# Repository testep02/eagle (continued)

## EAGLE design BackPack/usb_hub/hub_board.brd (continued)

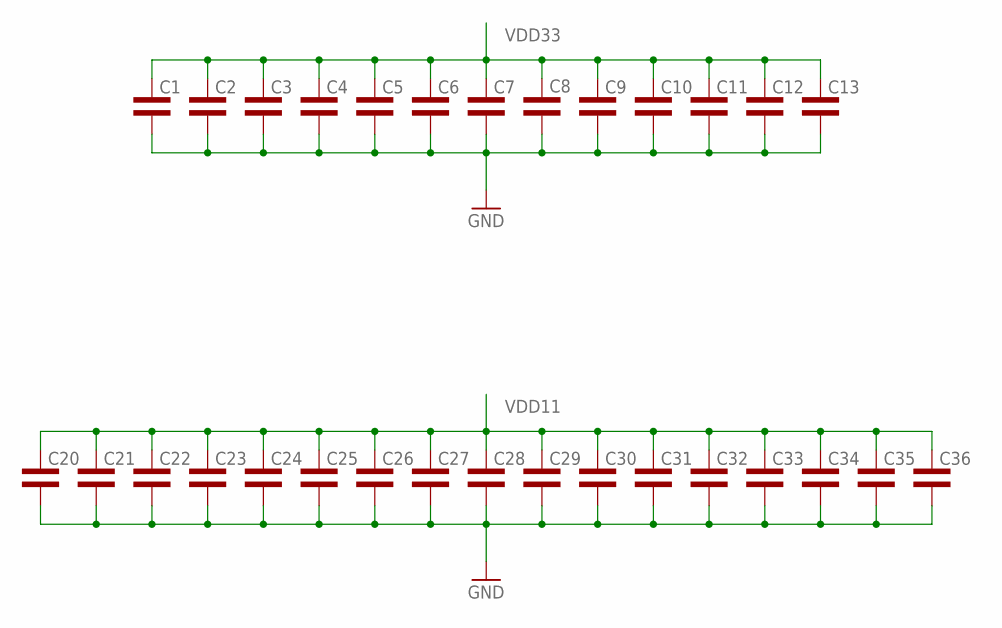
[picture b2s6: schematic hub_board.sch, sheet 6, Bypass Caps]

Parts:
C1, C2, C3, C4, C5, C6, C7, C8, C9, C10, C11, C12, C13, C20, C21, C22, C23, C24, C25, C26, C27, C28, C29, C30, C31, C32, C33, C34, C35, C36: CAP0402L3; 0402L3

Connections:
GND: C1.P$2 (2), C2.P$2 (2), C3.P$2 (2), C4.P$2 (2), C5.P$2 (2), C6.P$2 (2), C7.P$2 (2), C8.P$2 (2), C9.P$2 (2), C10.P$2 (2), C11.P$2 (2), C12.P$2 (2), C13.P$2 (2), C20.P$2 (2), C21.P$2 (2), C22.P$2 (2), C23.P$2 (2), C24.P$2 (2), C25.P$2 (2), C26.P$2 (2), C27.P$2 (2), C28.P$2 (2), C29.P$2 (2), C30.P$2 (2), C31.P$2 (2), C32.P$2 (2), C33.P$2 (2), C34.P$2 (2), C35.P$2 (2), C36.P$2 (2); also elsewhere on the board
VDD11: C20.P$1 (1), C21.P$1 (1), C22.P$1 (1), C23.P$1 (1), C24.P$1 (1), C25.P$1 (1), C26.P$1 (1), C27.P$1 (1), C28.P$1 (1), C29.P$1 (1), C30.P$1 (1), C31.P$1 (1), C32.P$1 (1), C33.P$1 (1), C34.P$1 (1), C35.P$1 (1), C36.P$1 (1); also elsewhere on the board
VDD33: C1.P$1 (1), C2.P$1 (1), C3.P$1 (1), C4.P$1 (1), C5.P$1 (1), C6.P$1 (1), C7.P$1 (1), C8.P$1 (1), C9.P$1 (1), C10.P$1 (1), C11.P$1 (1), C12.P$1 (1), C13.P$1 (1); also elsewhere on the board

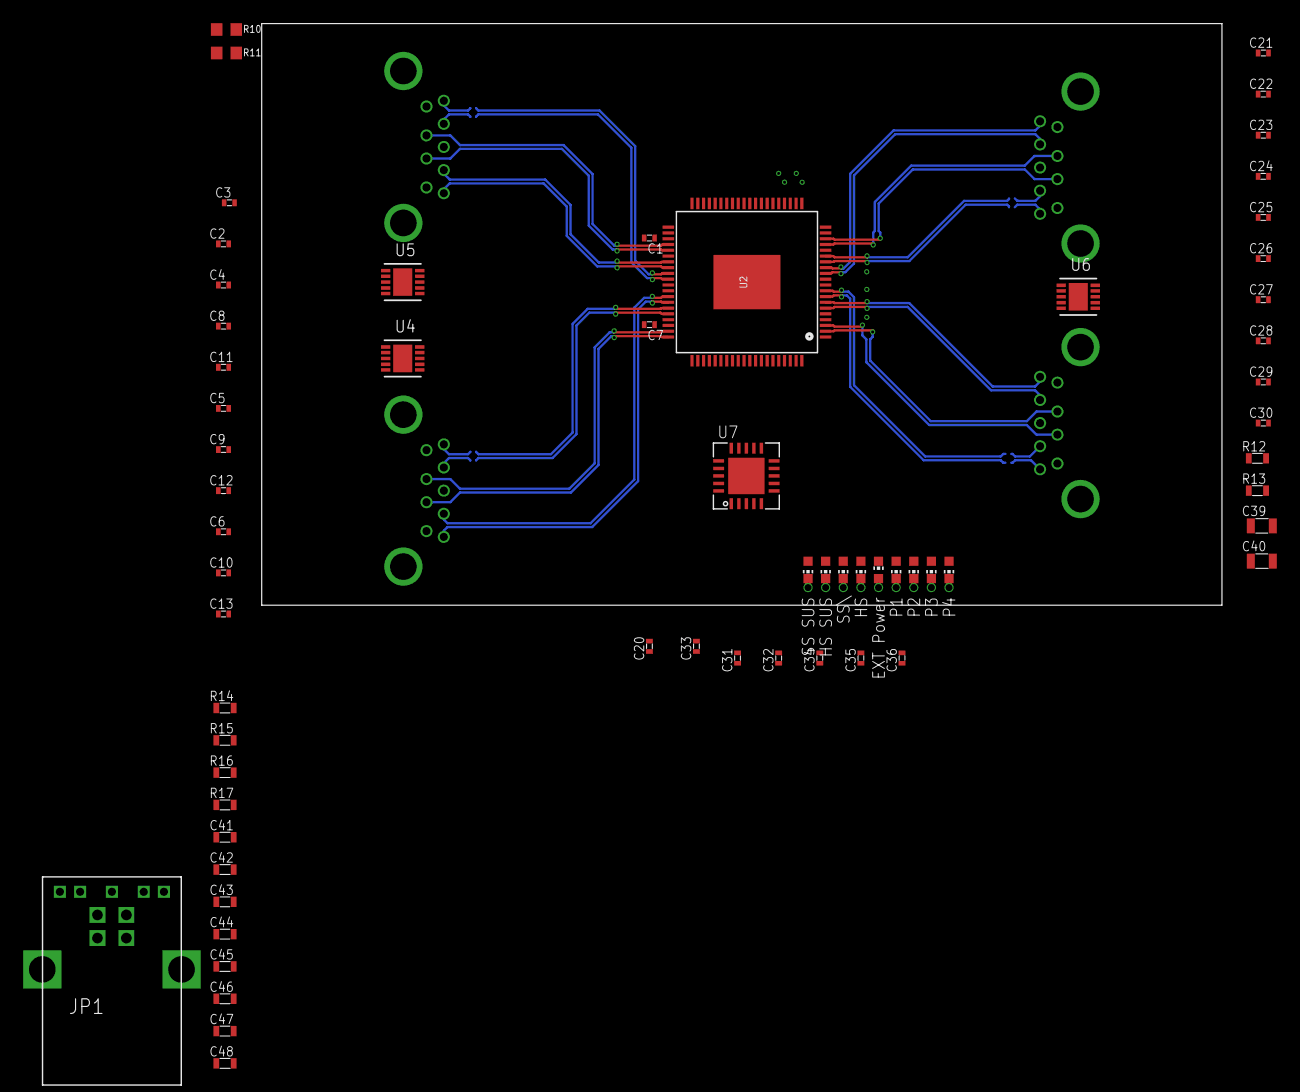
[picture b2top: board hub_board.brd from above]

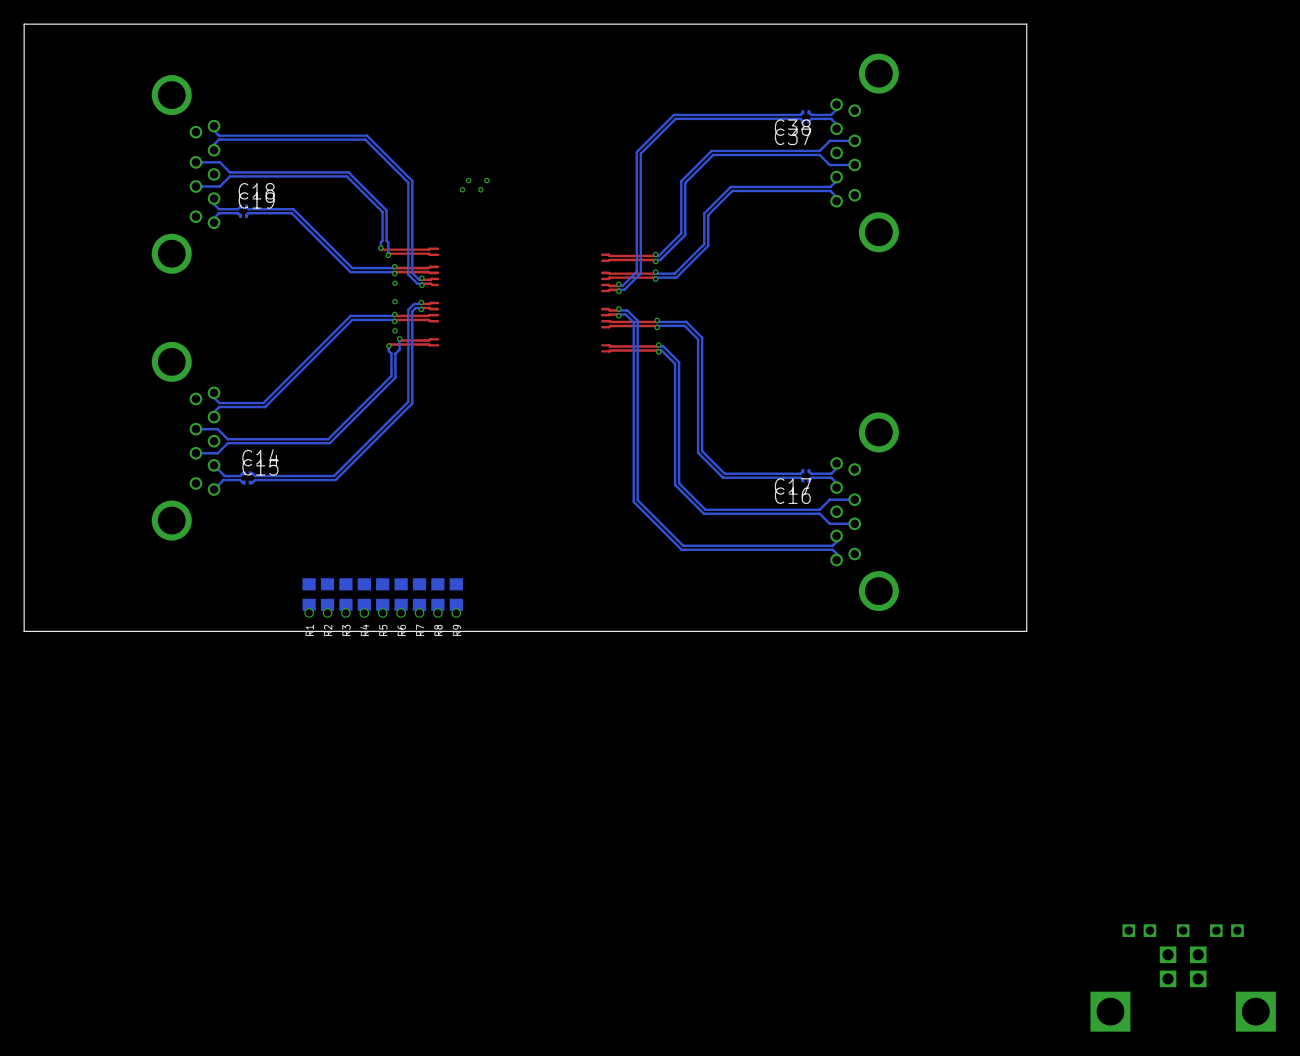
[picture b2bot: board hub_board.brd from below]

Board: 4 copper layers, 83.0 x 50.3 mm, 84 parts (17 on the bottom side), 59 nets.

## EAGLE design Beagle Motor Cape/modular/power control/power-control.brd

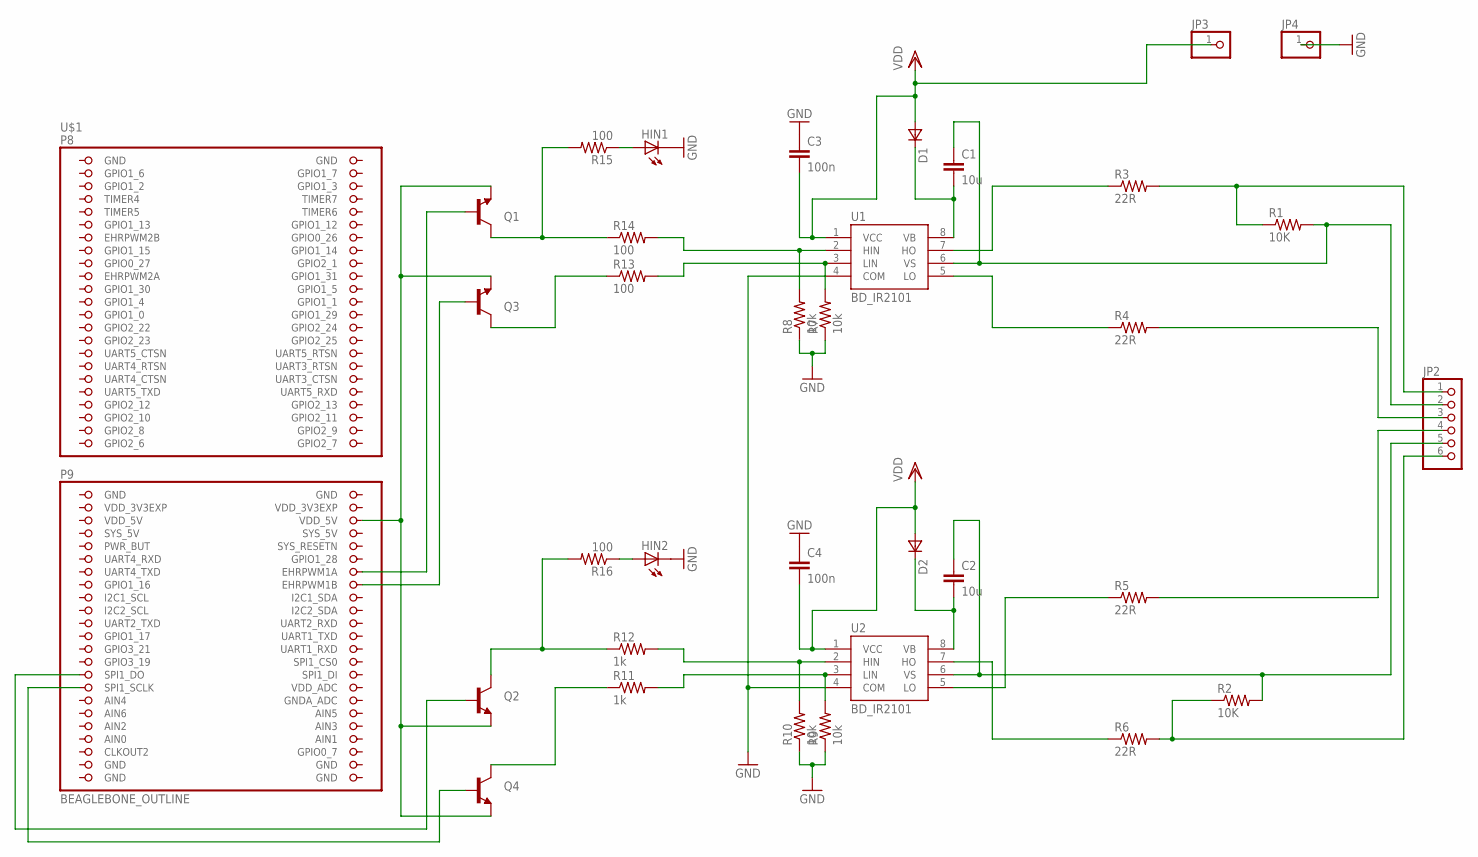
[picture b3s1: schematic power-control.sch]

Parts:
C1, C2: 10u; C0603
C3, C4: 100n; C0603
D1, D2: DSOT23; SOT-23
HIN1, HIN2: LEDCHIPLED_0603; CHIPLED_0603
JP2: PINHD-1X6; 1X06
JP3, JP4: PINHD-1X1; 1X01
Q1, Q2, Q3, Q4: TRANSISTOR_NPNSOT23-3; SOT23-3
R1, R2: 10K; R0603
R3, R4, R5, R6: 22R; R0603
R7, R8, R9, R10: 10k; R0603
R11, R12: 1k; R0603
R13, R14, R15, R16: 100; R0603
U1, U2: BD_IR2101; SO8
U$1: BEAGLEBONE_OUTLINE; BEAGLEBONE_SHIELD

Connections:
AIN0: U$1.85 (AIN0)
GND: C3.1, C4.1, HIN1.C, HIN2.C, JP4.1, R7.1, R8.1, R9.1, R10.1, U1.4 (COM), U2.4 (COM), U$1.1 (GND), U$1.2 (GND), U$1.47 (GND), U$1.48 (GND), U$1.89 (GND), U$1.90 (GND), U$1.91 (GND), U$1.92 (GND)
HO_1: R3.1, U1.7 (HO)
HO_2: R6.1, U2.7 (HO)
LO_1: R4.1, U1.5 (LO)
LO_2: R5.1, U2.5 (LO)
MOTOR_OUT_1: C1.1, JP2.2, R1.2, U1.6 (VS)
MOTOR_OUT_2: C2.1, JP2.5, R2.2, U2.6 (VS)
unnamed: Q1.1 (B), U$1.60 (EHRPWM1A)
unnamed: Q4.1 (B), U$1.77 (SPI1_SCLK)
unnamed: R8.2, R14.2, U1.2 (HIN)
unnamed: R7.2, R13.2, U1.3 (LIN)
unnamed: R10.2, R12.2, U2.2 (HIN)
unnamed: R9.2, R11.2, U2.3 (LIN)
unnamed: C1.2, D1.1 (C), U1.8 (VB)
unnamed: C2.2, D2.1 (C), U2.8 (VB)
unnamed: JP2.4, R5.2
unnamed: Q3.3 (C), R13.1
unnamed: Q3.1 (B), U$1.62 (EHRPWM1B)
unnamed: Q2.1 (B), U$1.75 (SPI1_DO)
unnamed: HIN1.A, R15.1
unnamed: JP2.1, R1.1, R3.2
unnamed: HIN2.A, R16.1
unnamed: Q2.3 (C), R12.1, R16.2
unnamed: Q1.3 (C), R14.1, R15.2
unnamed: Q4.3 (C), R11.1
unnamed: JP2.3, R4.2
unnamed: Q1.2 (E), Q2.2 (E), Q3.2 (E), Q4.2 (E), U$1.52 (VDD_5V)
unnamed: JP2.6, R2.1, R6.2
SYS_5V: U$1.53 (SYS_5V)
VDD: C3.2, C4.2, D1.3 (A), D2.3 (A), JP3.1, U1.1 (VCC), U2.1 (VCC)
VDD_3V3EXP: U$1.49 (VDD_3V3EXP), U$1.50 (VDD_3V3EXP)
VDD_5V: U$1.51 (VDD_5V)

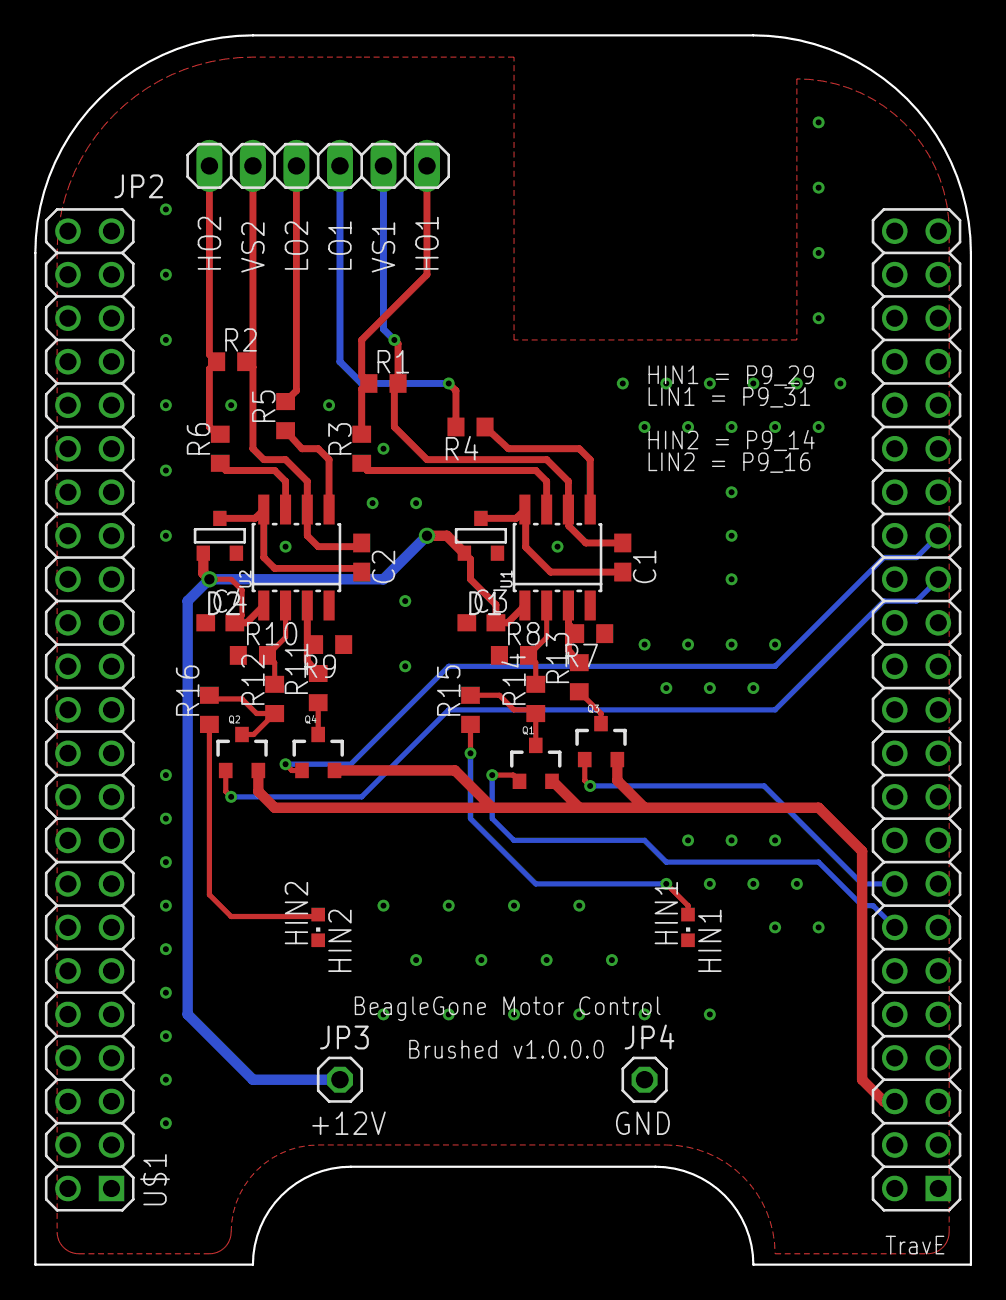
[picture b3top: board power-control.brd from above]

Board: 2 copper layers, 54.6 x 71.8 mm, 34 parts (0 on the bottom side), 30 nets.

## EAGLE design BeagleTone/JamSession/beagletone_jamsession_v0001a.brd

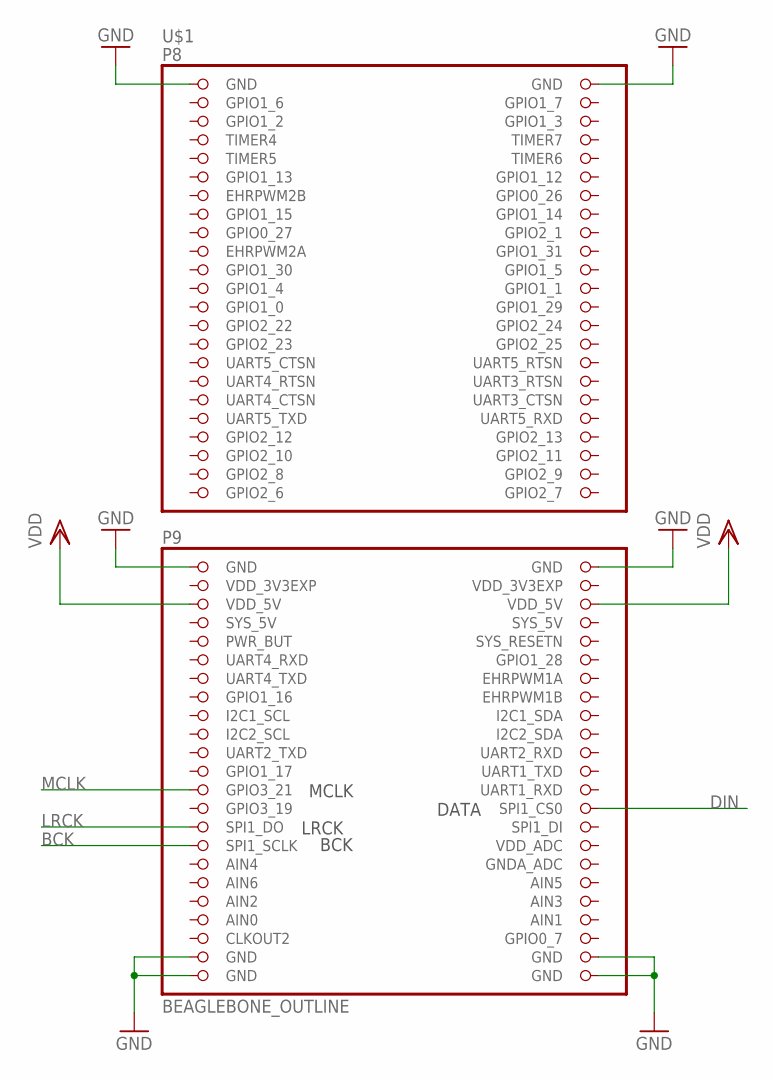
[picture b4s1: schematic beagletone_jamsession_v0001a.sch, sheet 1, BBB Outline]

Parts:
U$1: BEAGLEBONE_OUTLINE; BEAGLEBONE_SHIELD

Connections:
AIN0: U$1.85 (AIN0)
BCK: U$1.77 (SPI1_SCLK); also elsewhere on the board
DIN: U$1.74 (SPI1_CS0); also elsewhere on the board
GND: U$1.1 (GND), U$1.2 (GND), U$1.47 (GND), U$1.48 (GND), U$1.89 (GND), U$1.90 (GND), U$1.91 (GND), U$1.92 (GND); also elsewhere on the board
LRCK: U$1.75 (SPI1_DO); also elsewhere on the board
MCLK: U$1.71 (GPIO3_21)
SYS_5V: U$1.53 (SYS_5V)
VDD: U$1.51 (VDD_5V), U$1.52 (VDD_5V); also elsewhere on the board
VDD_3V3EXP: U$1.49 (VDD_3V3EXP), U$1.50 (VDD_3V3EXP)

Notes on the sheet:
MCLK
LRCK
BCK
DATA

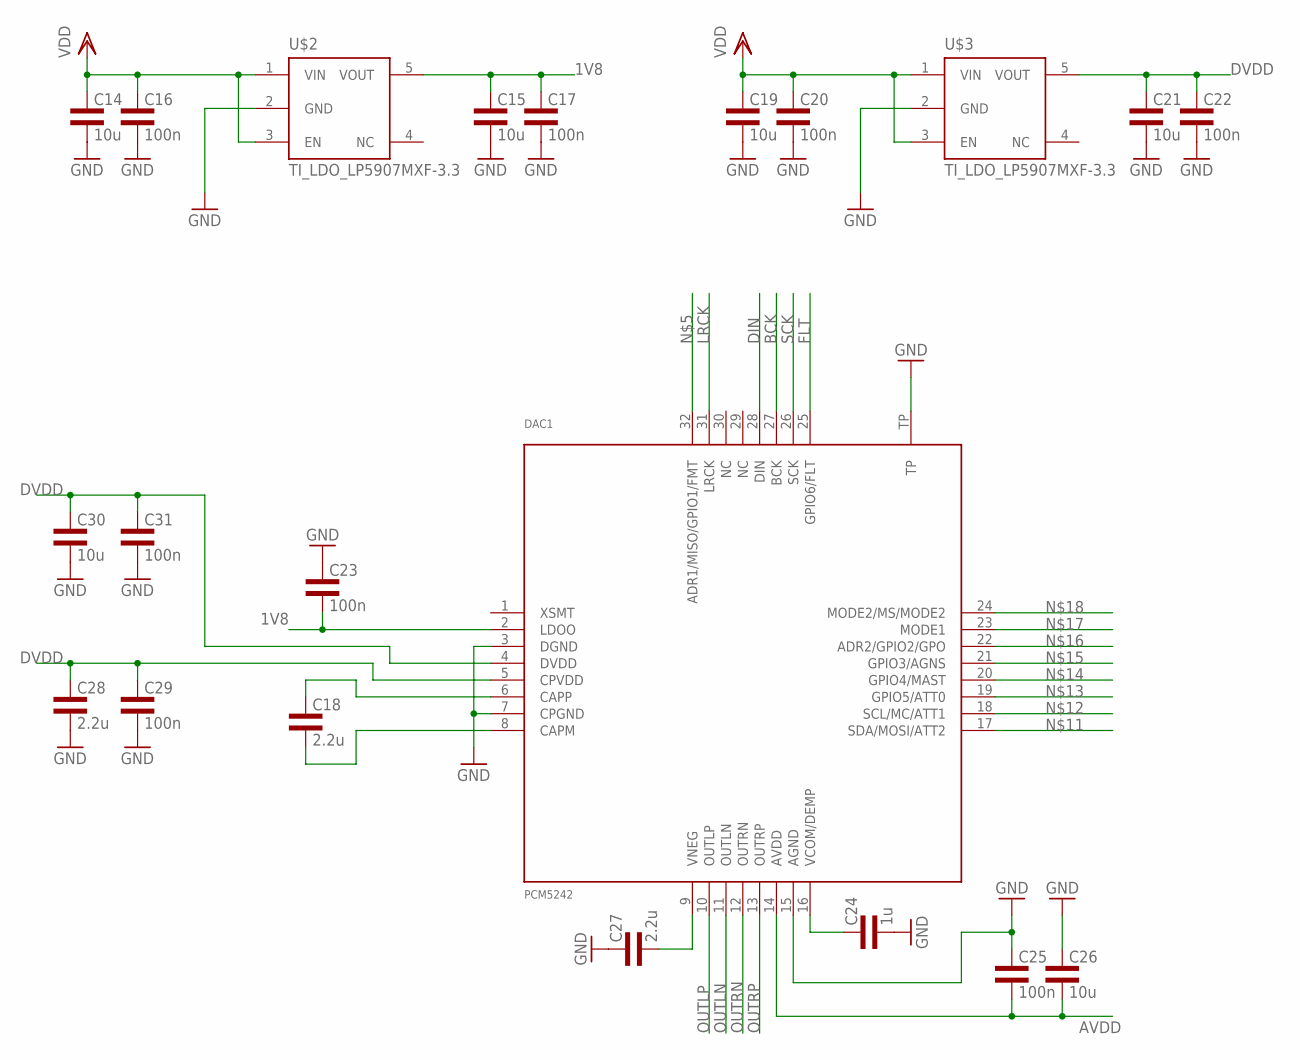
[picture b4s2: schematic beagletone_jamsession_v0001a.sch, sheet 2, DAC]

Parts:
C14, C15, C19, C21: 10u; 0805L3
C16, C17, C20, C22: 100n; 0603L3
C18, C27, C28: 2.2u; 0805L3
C23, C25, C29, C31: 100n; 0402L3
C24: 1u; 0603L3
C26, C30: 10u; 0603L3
DAC1: PCM5242; S-PVQFN-N32
U$2, U$3: TI_LDO_LP5907MXF-3.3; TI_LDO_SOT-23

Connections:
1V8: C15.1, C17.P$1 (1), C23.P$2 (2), DAC1.2 (LDOO), U$2.5 (VOUT)
AVDD: C25.P$2 (2), C26.P$2 (2), DAC1.14 (AVDD); also elsewhere on the board
BCK: DAC1.27 (BCK); also elsewhere on the board
DIN: DAC1.28 (DIN); also elsewhere on the board
DVDD: C21.1, C22.P$1 (1), C28.1, C29.P$1 (1), C30.P$1 (1), C31.P$1 (1), DAC1.4 (DVDD), DAC1.5 (CPVDD), U$3.5 (VOUT)
FLT: DAC1.25 (GPIO6/FLT)
GND: C14.2, C15.2, C16.P$2 (2), C17.P$2 (2), C19.2, C20.P$2 (2), C21.2, C22.P$2 (2), C23.P$1 (1), C24.P$2 (2), C25.P$1 (1), C26.P$1 (1), C27.1, C28.2, C29.P$2 (2), C30.P$2 (2), C31.P$2 (2), DAC1.3 (DGND), DAC1.7 (CPGND), DAC1.15 (AGND), DAC1.TP, U$2.2 (GND), U$3.2 (GND); also elsewhere on the board
LRCK: DAC1.31 (LRCK); also elsewhere on the board
unnamed: C18.1, DAC1.6 (CAPP)
unnamed: C18.2, DAC1.8 (CAPM)
unnamed: C24.P$1 (1), DAC1.16 (VCOM/DEMP)
unnamed: C27.2, DAC1.9 (VNEG)
OUTLN: DAC1.11 (OUTLN); also elsewhere on the board
OUTLP: DAC1.10 (OUTLP); also elsewhere on the board
OUTRN: DAC1.12 (OUTRN); also elsewhere on the board
OUTRP: DAC1.13 (OUTRP); also elsewhere on the board
SCK: DAC1.26 (SCK)
VDD: C14.1, C16.P$1 (1), C19.1, C20.P$1 (1), U$2.1 (VIN), U$2.3 (EN), U$3.1 (VIN), U$3.3 (EN); also elsewhere on the board

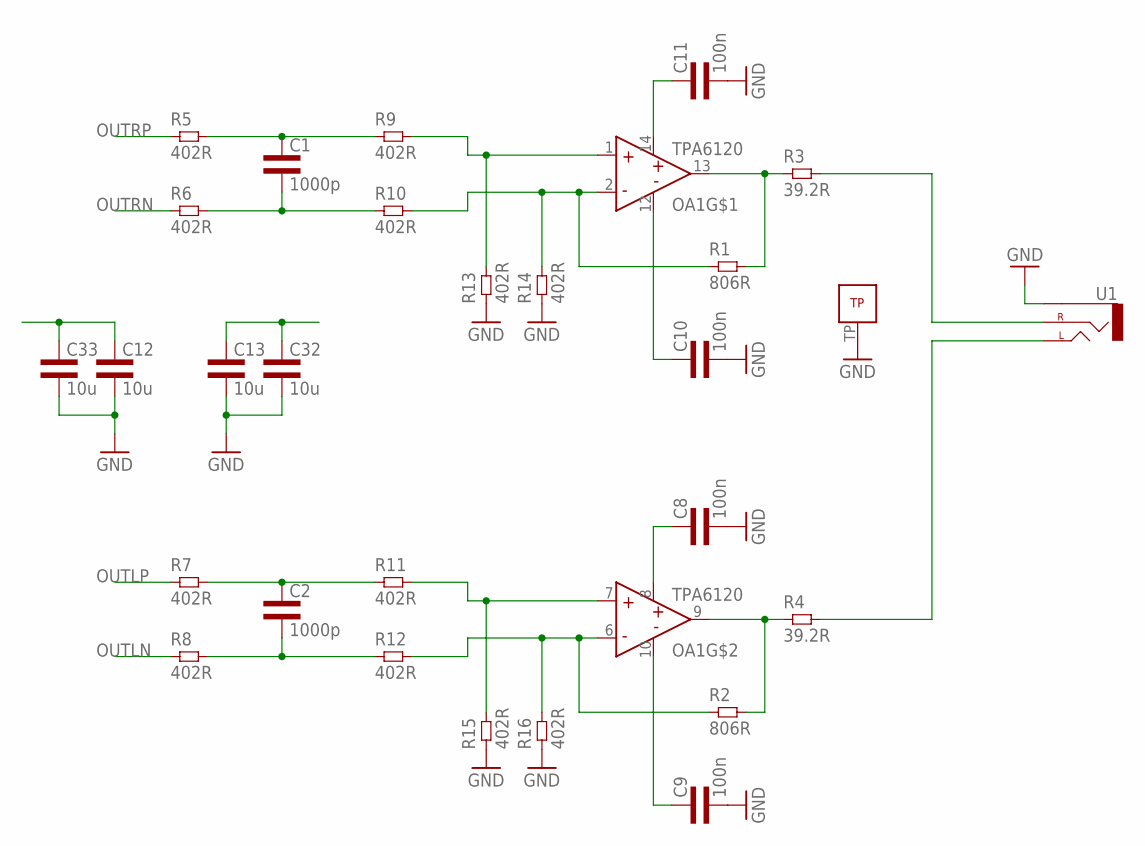
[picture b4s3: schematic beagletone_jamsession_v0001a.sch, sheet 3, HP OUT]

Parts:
C1, C2: 1000p; 0603L3
C8, C9, C10, C11: 100n; 0603L3
C12, C13, C32, C33: 10u; 0603L3
OA1: TPA6120QFN; S-PVQFN-N14
R1, R2: 806R; 0603L3
R3, R4: 39.2R; 0805L3
R5, R6, R7, R8, R9, R10, R11, R12, R13, R14, R15, R16: 402R; 0603L3
U1: AUDIO-JACKSMD2; AUDIO-JACK-3.5MM-SMD

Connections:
GND: C8.P$2 (2), C9.P$2 (2), C10.P$2 (2), C11.P$2 (2), C12.P$2 (2), C13.P$2 (2), C32.P$2 (2), C33.P$2 (2), OA1.TP, R13.P$1 (1), R14.P$1 (1), R15.P$1 (1), R16.P$1 (1), U1.SLEEVE; also elsewhere on the board
unnamed: OA1.13 (OUT), R1.P$2 (2), R3.1
unnamed: OA1.2 (IN-), R1.P$1 (1), R10.P$2 (2), R14.P$2 (2)
unnamed: OA1.9 (OUT), R2.P$2 (2), R4.1
unnamed: OA1.6 (IN-), R2.P$1 (1), R12.P$2 (2), R16.P$2 (2)
unnamed: OA1.7 (IN+), R11.P$2 (2), R15.P$2 (2)
unnamed: C2.P$2 (2), R8.P$2 (2), R12.P$1 (1)
unnamed: C2.P$1 (1), R7.P$2 (2), R11.P$1 (1)
unnamed: OA1.1 (IN+), R9.P$2 (2), R13.P$2 (2)
unnamed: C1.P$1 (1), R5.P$2 (2), R9.P$1 (1)
unnamed: C1.P$2 (2), R6.P$2 (2), R10.P$1 (1)
unnamed: R3.2, U1.RING (RIGHT)
unnamed: R4.2, U1.TIP (LEFT)
OUTLN: R8.P$1 (1); also elsewhere on the board
OUTLP: R7.P$1 (1); also elsewhere on the board
OUTRN: R6.P$1 (1); also elsewhere on the board
OUTRP: R5.P$1 (1); also elsewhere on the board
VCC+: C8.P$1 (1), C11.P$1 (1), C12.P$1 (1), C33.P$1 (1), OA1.8 (V+), OA1.14 (V+); also elsewhere on the board
VCC-: C9.P$1 (1), C10.P$1 (1), C13.P$1 (1), C32.P$1 (1), OA1.10 (V-), OA1.12 (V-); also elsewhere on the board

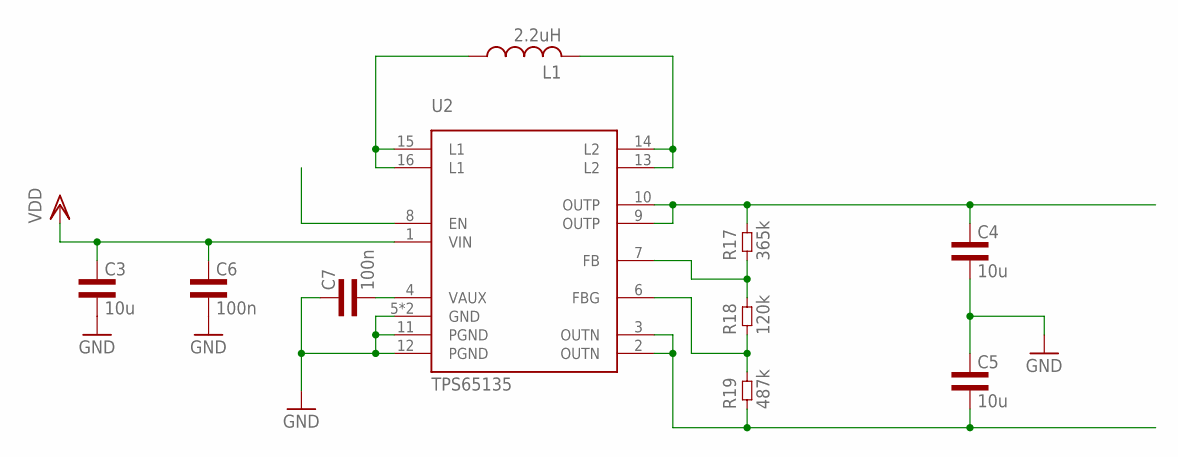
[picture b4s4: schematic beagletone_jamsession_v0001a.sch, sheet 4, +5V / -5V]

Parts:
C3, C4, C5: 10u; 0805L3
C6, C7: 100n; 0603L3
L1: 2.2uH; 2520
R17: 365k; 0805L3
R18: 120k; 0805L3
R19: 487k; 0805L3
U2: TPS65135; S-PWQFN-N16_RTE

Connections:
EN: U2.8 (EN)
FB: R17.1, R18.2, U2.7 (FB)
FBG: R18.1, R19.2, U2.6 (FBG)
GND: C3.2, C4.2, C5.1, C6.P$2 (2), C7.P$1 (1), U2.5 (GND), U2.11 (PGND), U2.12 (PGND), U2.P$1 (GND); also elsewhere on the board
L1: L1.1, U2.15 (L1), U2.16 (L1)
L2: L1.2, U2.13 (L2), U2.14 (L2)
VAUX: C7.P$2 (2), U2.4 (VAUX)
VCC+: C4.1, R17.2, U2.9 (OUTP), U2.10 (OUTP); also elsewhere on the board
VCC-: C5.2, R19.1, U2.2 (OUTN), U2.3 (OUTN); also elsewhere on the board
VDD: C3.1, C6.P$1 (1), U2.1 (VIN); also elsewhere on the board

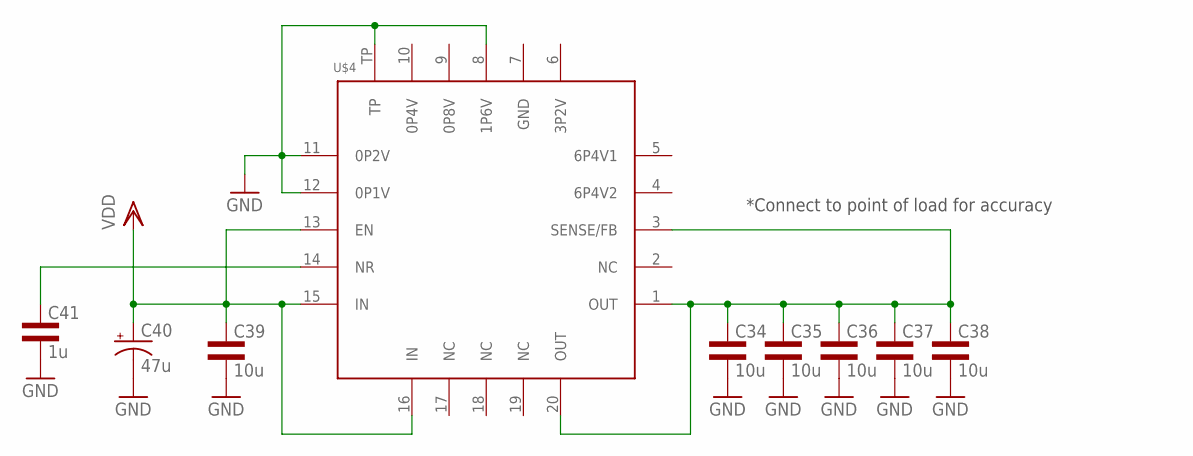
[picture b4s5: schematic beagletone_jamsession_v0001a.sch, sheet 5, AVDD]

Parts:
C34, C35, C36, C37, C38, C39: 10u; 0603L3
C40: 47u; CT3216
C41: 1u; 0603L3
U$4: POWER-SUPPLY_POS_V1_TI_LDO_TPS7A4700; POWER-SUPPLY_POS_V1_TI_LDO_VQFN-20

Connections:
AVDD: C34.P$1 (1), C35.P$1 (1), C36.P$1 (1), C37.P$1 (1), C38.P$1 (1), U$4.1 (OUT), U$4.3 (SENSE/FB), U$4.20 (OUT); also elsewhere on the board
GND: C34.P$2 (2), C35.P$2 (2), C36.P$2 (2), C37.P$2 (2), C38.P$2 (2), C39.P$2 (2), C40.-, C41.P$2 (2), U$4.8 (1P6V), U$4.11 (0P2V), U$4.12 (0P1V), U$4.TP; also elsewhere on the board
unnamed: C41.P$1 (1), U$4.14 (NR)
VDD: C39.P$1 (1), C40.+, U$4.13 (EN), U$4.15 (IN), U$4.16 (IN); also elsewhere on the board

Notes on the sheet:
*Connect to point of load for accuracy

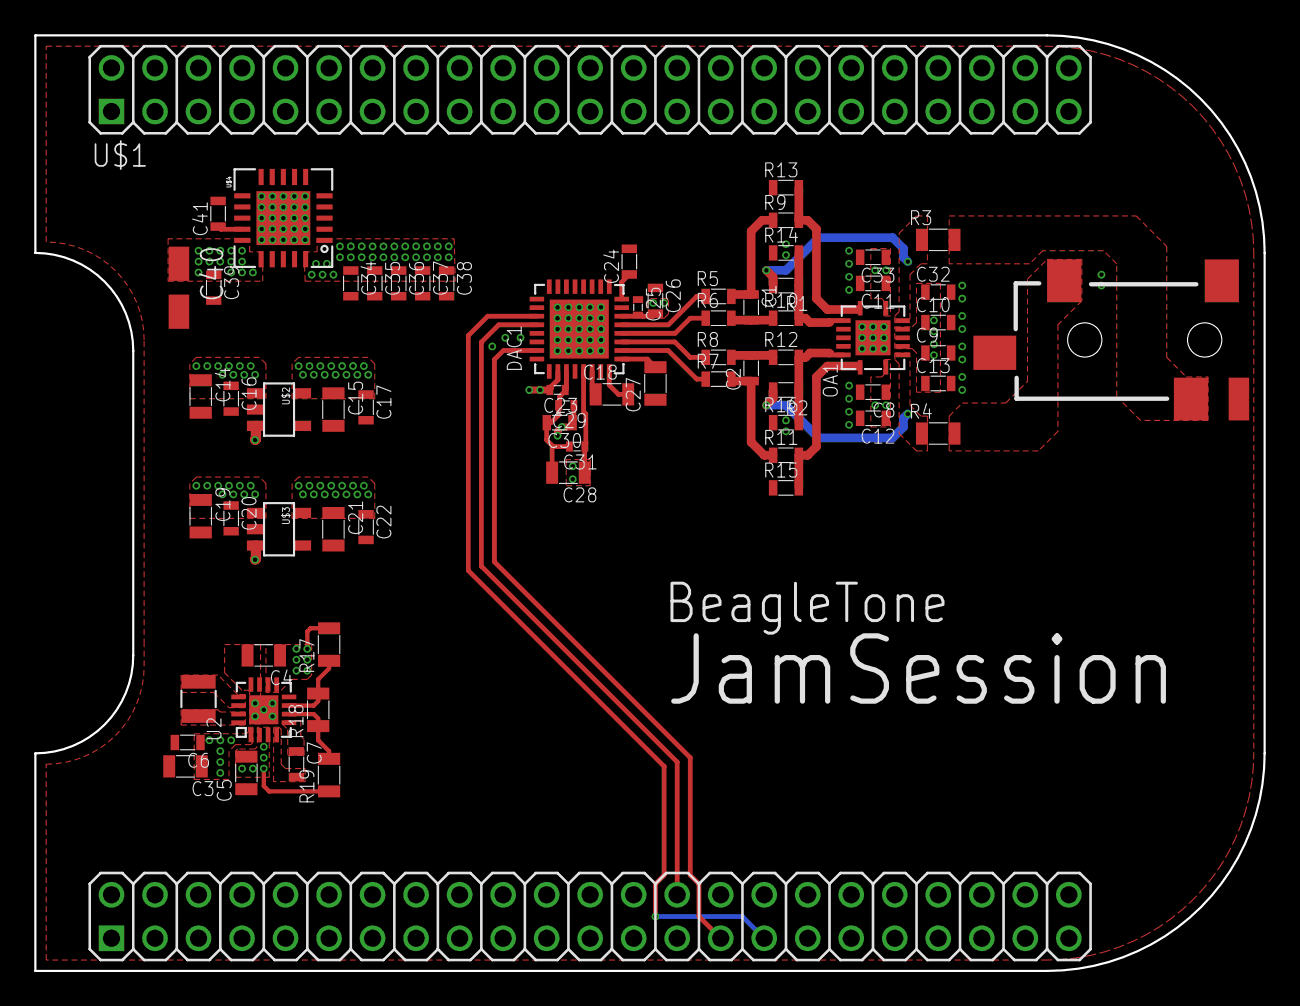
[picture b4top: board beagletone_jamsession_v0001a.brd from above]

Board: 4 copper layers, 71.8 x 54.6 mm, 69 parts (0 on the bottom side), 37 nets.

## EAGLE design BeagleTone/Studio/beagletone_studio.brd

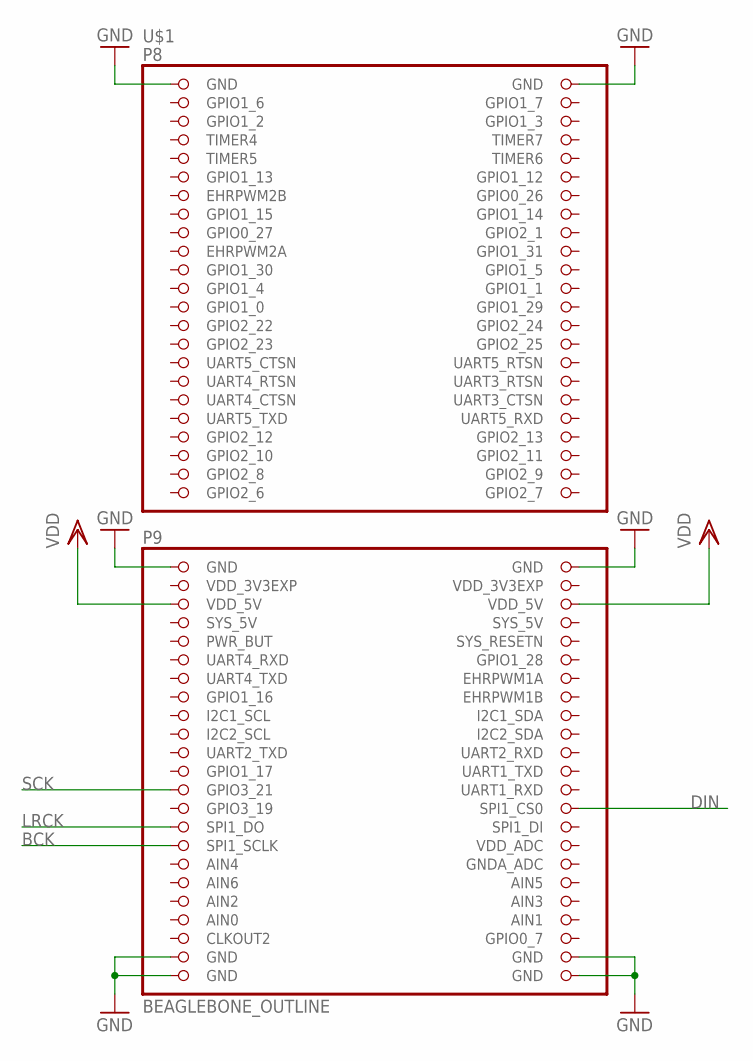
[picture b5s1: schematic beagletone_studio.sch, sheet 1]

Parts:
U$1: BEAGLEBONE_OUTLINE; BEAGLEBONE_SHIELD

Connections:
AIN0: U$1.85 (AIN0)
BCK: U$1.77 (SPI1_SCLK); also elsewhere on the board
DIN: U$1.74 (SPI1_CS0); also elsewhere on the board
GND: U$1.1 (GND), U$1.2 (GND), U$1.47 (GND), U$1.48 (GND), U$1.89 (GND), U$1.90 (GND), U$1.91 (GND), U$1.92 (GND); also elsewhere on the board
LRCK: U$1.75 (SPI1_DO); also elsewhere on the board
SCK: U$1.71 (GPIO3_21); also elsewhere on the board
SYS_5V: U$1.53 (SYS_5V)
VDD: U$1.51 (VDD_5V), U$1.52 (VDD_5V); also elsewhere on the board
VDD_3V3EXP: U$1.49 (VDD_3V3EXP), U$1.50 (VDD_3V3EXP)

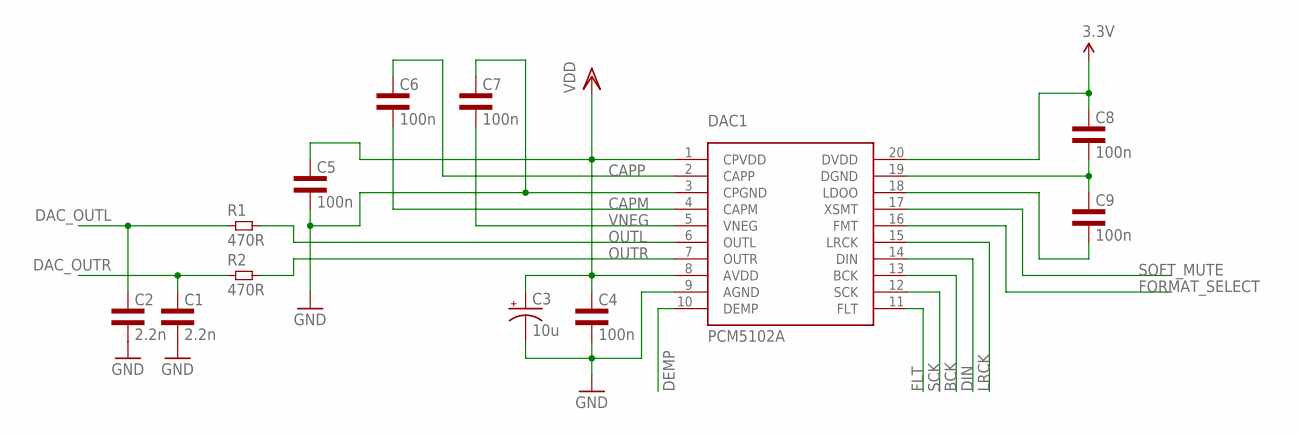
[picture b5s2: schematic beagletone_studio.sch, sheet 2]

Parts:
C1, C2: 2.2n; 0603L3
C3: 10u; CT3216
C4, C5, C6, C7: 100n; 0603L3
C8, C9: 100n; 0402L3
DAC1: PCM5102A; R-PDSO-G20_65
R1, R2: 470R; 0603L3

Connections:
3.3V: C8.P$1 (1), DAC1.20 (DVDD)
BCK: DAC1.13 (BCK); also elsewhere on the board
CAPM: C6.P$2 (2), DAC1.4 (CAPM)
CAPP: C6.P$1 (1), DAC1.2 (CAPP)
DAC_OUTL: C2.P$1 (1), R1.P$1 (1); also elsewhere on the board
DAC_OUTR: C1.P$1 (1), R2.P$1 (1); also elsewhere on the board
DEMP: DAC1.10 (DEMP)
DIN: DAC1.14 (DIN); also elsewhere on the board
FLT: DAC1.11 (FLT)
FORMAT_SELECT: DAC1.16 (FMT)
GND: C1.P$2 (2), C2.P$2 (2), C3.-, C4.P$2 (2), C5.P$2 (2), C7.P$1 (1), DAC1.3 (CPGND), DAC1.9 (AGND); also elsewhere on the board
LRCK: DAC1.15 (LRCK); also elsewhere on the board
unnamed: C8.P$2 (2), C9.P$1 (1), DAC1.19 (DGND)
unnamed: C9.P$2 (2), DAC1.18 (LDOO)
OUTL: DAC1.6 (OUTL), R1.P$2 (2)
OUTR: DAC1.7 (OUTR), R2.P$2 (2)
SCK: DAC1.12 (SCK); also elsewhere on the board
SOFT_MUTE: DAC1.17 (XSMT)
VDD: C3.+, C4.P$1 (1), C5.P$1 (1), DAC1.1 (CPVDD), DAC1.8 (AVDD); also elsewhere on the board
VNEG: C7.P$2 (2), DAC1.5 (VNEG)

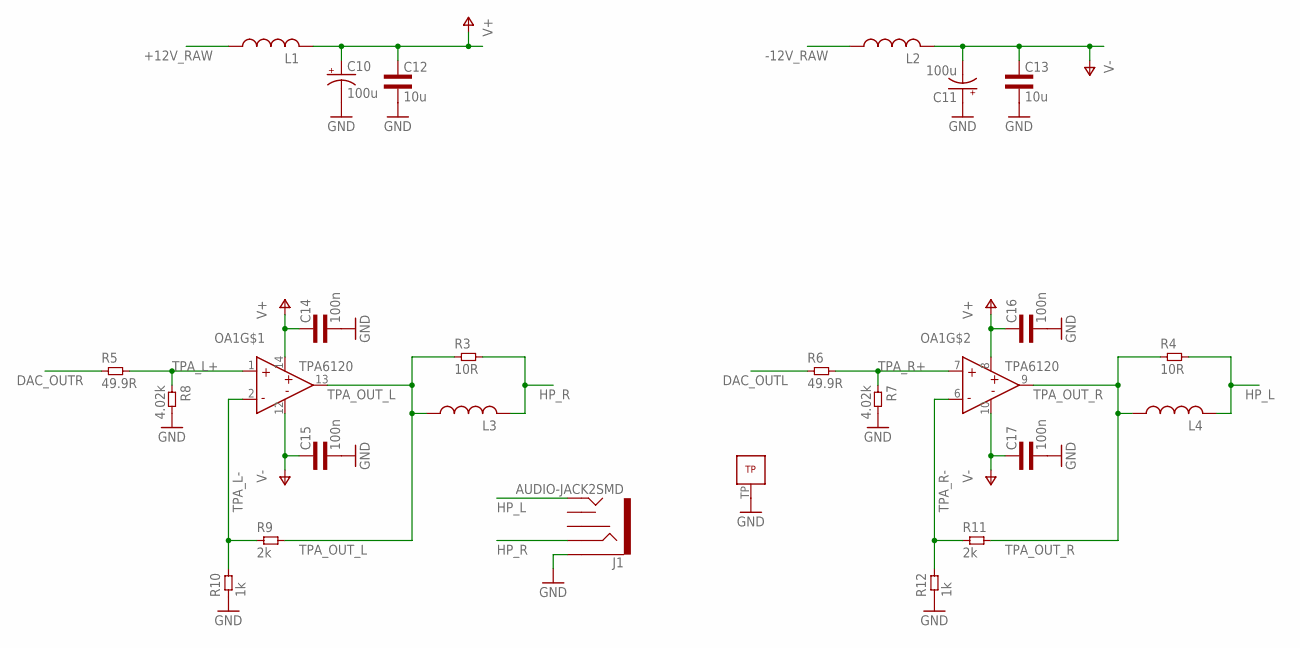
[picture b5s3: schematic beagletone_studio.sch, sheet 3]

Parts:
C10, C11: 100u; CT7343
C12, C13: 10u; 0805L3
C14, C15, C16, C17: 100n; 0603L3
J1: AUDIO-JACK2SMD; AUDIO-JACK-3.5MM-SMD
L1, L2, L3, L4: L-USL2012C; L2012C
OA1: TPA6120QFN; S-PVQFN-N14
R3, R4: 10R; 0805L3
R5, R6: 49.9R; 0603L3
R7, R8: 4.02k; 0603L3
R9, R11: 2k; 0603L3
R10, R12: 1k; 0603L3

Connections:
+12V_RAW: L1.1
-12V_RAW: L2.1
DAC_OUTL: R6.P$1 (1); also elsewhere on the board
DAC_OUTR: R5.P$1 (1); also elsewhere on the board
GND: C10.-, C11.+, C12.2, C13.2, C14.P$2 (2), C15.P$2 (2), C16.P$2 (2), C17.P$2 (2), J1.SLEEVE, OA1.TP, R7.P$2 (2), R8.P$2 (2), R10.P$1 (1), R12.P$1 (1); also elsewhere on the board
HP_L: J1.TIP, L4.2, R4.2
HP_R: J1.RING, L3.2, R3.2
TPA_L+: OA1.1 (IN+), R5.P$2 (2), R8.P$1 (1)
TPA_L-: OA1.2 (IN-), R9.P$1 (1), R10.P$2 (2)
TPA_OUT_L: L3.1, OA1.13 (OUT), R3.1, R9.P$2 (2)
TPA_OUT_R: L4.1, OA1.9 (OUT), R4.1, R11.P$2 (2)
TPA_R+: OA1.7 (IN+), R6.P$2 (2), R7.P$1 (1)
TPA_R-: OA1.6 (IN-), R11.P$1 (1), R12.P$2 (2)
V+: C10.+, C12.1, C14.P$1 (1), C16.P$1 (1), L1.2, OA1.8 (V+), OA1.14 (V+)
V-: C11.-, C13.1, C15.P$1 (1), C17.P$1 (1), L2.2, OA1.10 (V-), OA1.12 (V-)

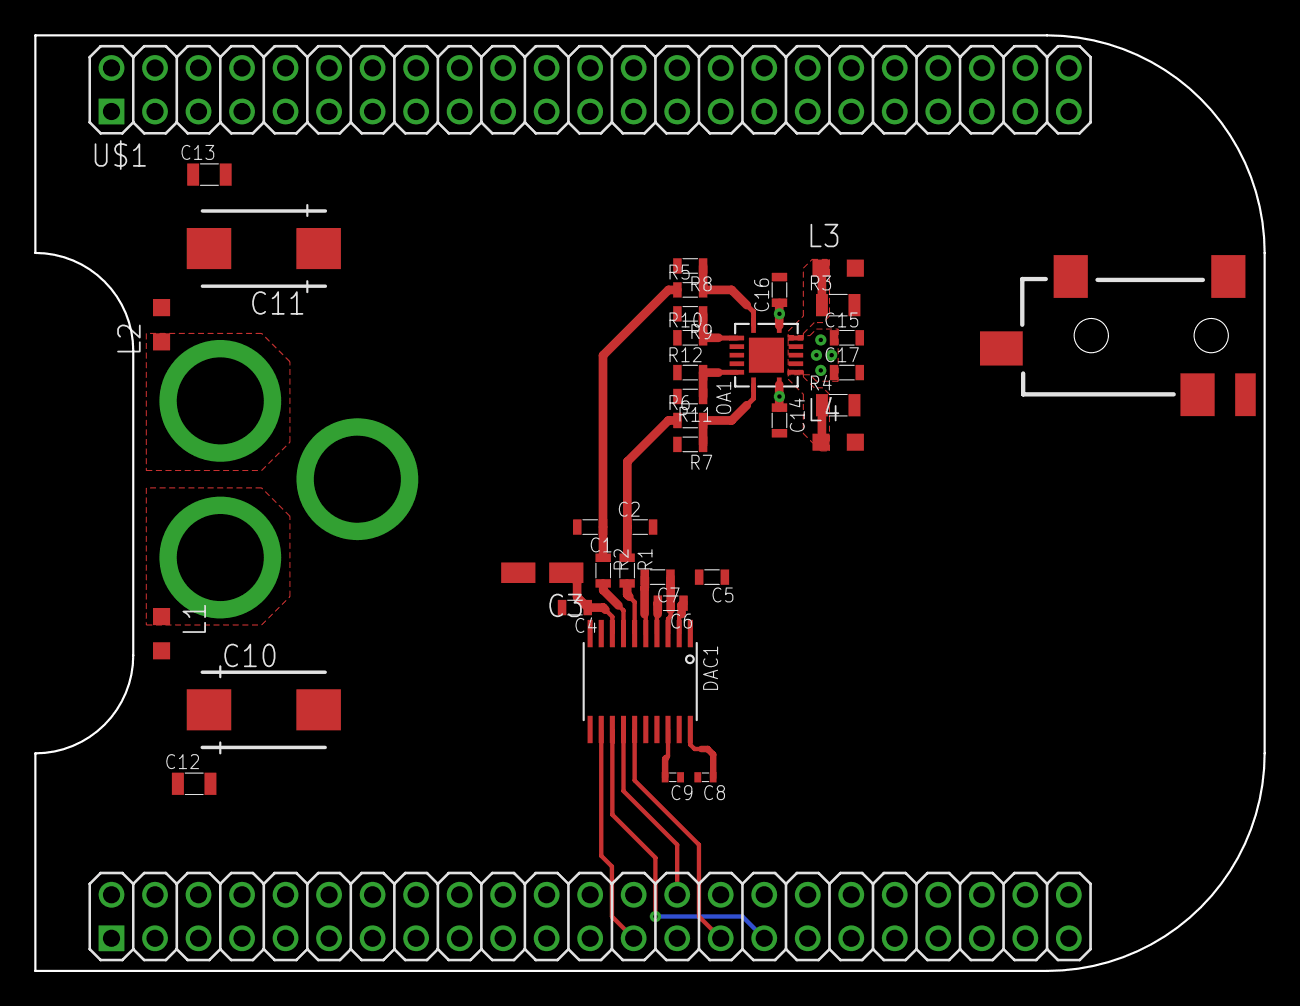
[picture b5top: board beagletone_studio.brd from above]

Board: 2 copper layers, 71.8 x 54.6 mm, 37 parts (0 on the bottom side), 27 nets.
